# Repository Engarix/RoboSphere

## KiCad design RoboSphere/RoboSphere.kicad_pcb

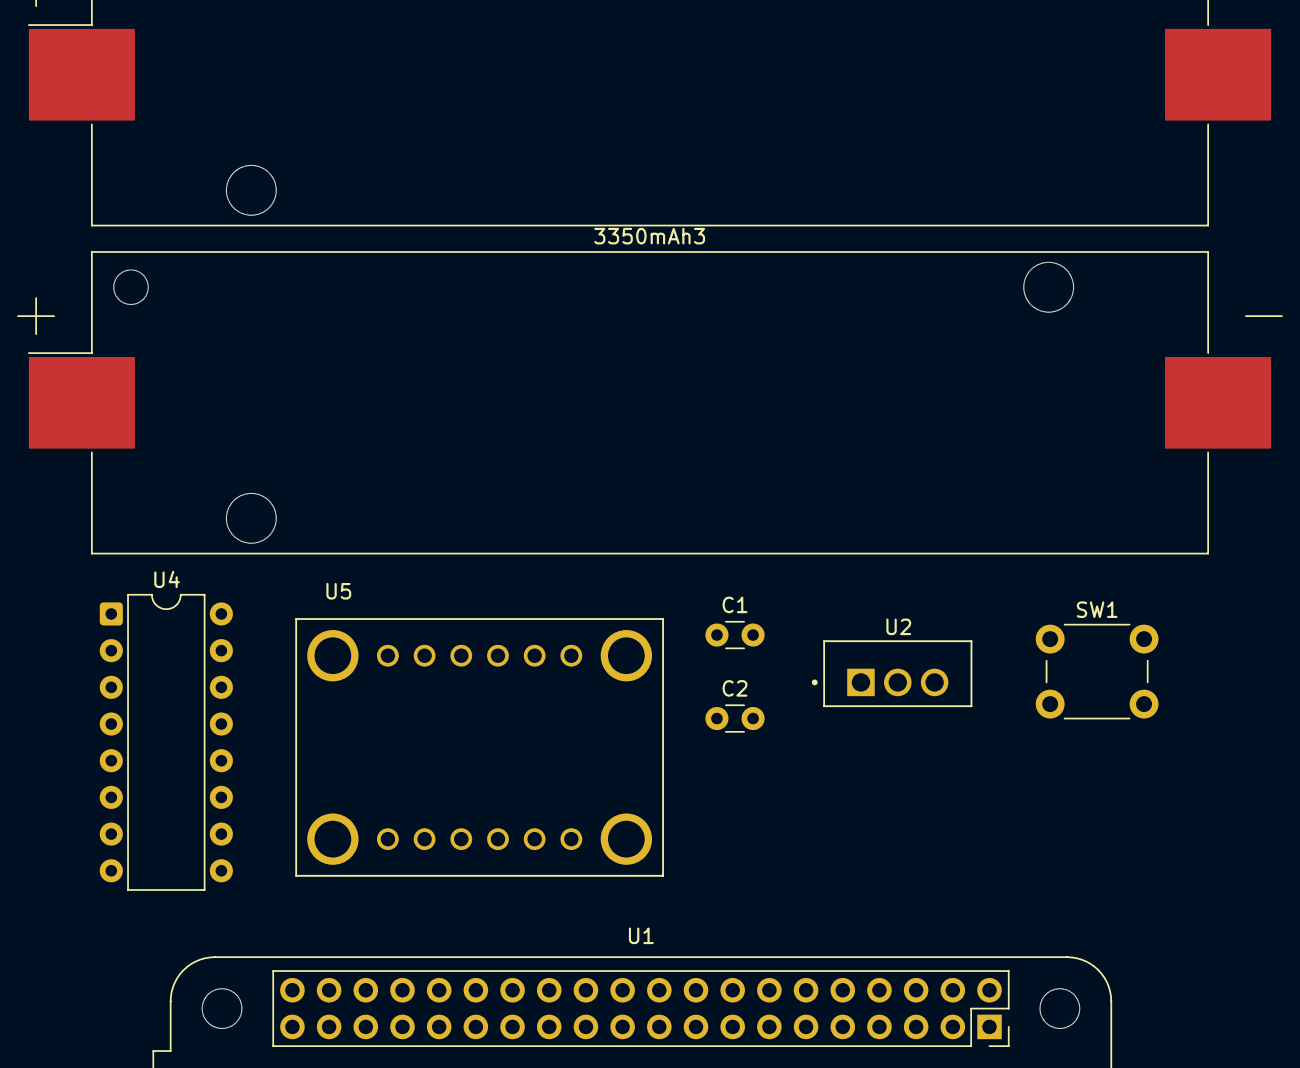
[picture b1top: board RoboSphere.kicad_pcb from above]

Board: 2 copper layers, 9 parts (0 on the bottom side), 16 nets, no tracks yet.

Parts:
3350mAh2, 3350mAh3: 3.7V; BatteryHolder_Keystone_1042_1x18650
C1, C2: C; C_Disc_D3.0mm_W1.6mm_P2.50mm
SW1: SW_Push; SW_PUSH_6mm
U1: RASPBERRY_PI_ZERO_2_W; Raspberry_Pi_Zero_Socketed_THT_FaceDown_MountingHoles
U2: L7806; TO255P1020X450X1968-3B
U4: L293D; DIP-16_W7.62mm
U5: ADS1115 1085; MODULE_1085

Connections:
+6V: C2.2, U2.3 (OUT)
+7.5V: C1.2, SW1.2, U2.1 (IN), U4.8 (VCC2), U4.16 (VCC1), U5.JP1_5 (A0)
GND: 3350mAh2.2 (-), C1.1, C2.1, U2.2 (GND), U4.4 (GND), U4.5 (GND), U4.12 (GND), U4.13 (GND), U5.JP2_2 (GND), U5.JP2_5 (ADDR)
unnamed: 3350mAh2.1 (+), 3350mAh3.2 (-)
unnamed: 3350mAh3.1 (+), SW1.1
unnamed: U1.1 (3V3_1), U5.JP2_1 (VIN)
unnamed: U1.3 (GPIO2/SDA1), U5.JP2_4 (SDA)
unnamed: U1.5 (GPIO3/SCL), U5.JP2_3 (SCL)
unnamed: U1.29 (GPIO5), U5.JP2_6 (ALRT)
unnamed: U1.26 (GPIO7/SPI_~CE1), U4.15 (4A)
unnamed: U1.24 (GPIO8/SPI_~CE0), U4.10 (3A)
unnamed: U1.33 (GPIO13), U4.9 (EN3,4)
unnamed: U1.35 (GPIO19), U4.1 (EN1,2)
unnamed: U1.16 (GPIO23/GPIO_GEN4), U4.2 (1A)
unnamed: U1.18 (GPIO24/GPIO_GEN5), U4.7 (2A)
unnamed: U5.SH1 (SHIELD), U5.SH2 (SHIELD), U5.SH3 (SHIELD), U5.SH4 (SHIELD)

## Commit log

2025-03-26 KiCad Start
2025-04-05 Autodesk Model RoboSphere
2025-04-12 KiCad Update
2025-04-12 KiCad Update 0.2
2025-04-15 Kicad H-bridge update
2025-04-18 Power Converter Module
2025-04-18 Power % module
2025-04-19 Setting values
2025-04-19 Power Management Updates
2025-05-24 Power module update & ADC
2025-10-28 Finished Version 1
2025-10-28 Just making sure everything is updated
2025-11-03 Updated schematic with placement organization
2026-01-02 Printer Files
2026-01-06 Update on 3d model
2026-01-06 Started Coding
2026-01-06 Controller DONE
2026-01-09 Received V1
2026-01-10 Constant connecting
2026-01-11 Thesis
2026-01-11 Pictures
2026-01-11 Thesis V1 (still needs pictures and modified power module)
2026-01-11 Thesis Finished V2
2026-01-14 Kod działa
2026-01-16 Thesis V3
2026-01-16 Thesis V3.1
2026-01-29 Bigger pin, screw holes
2026-02-07 3D prints update
2026-02-19 Bridge 3.0 & Lock
